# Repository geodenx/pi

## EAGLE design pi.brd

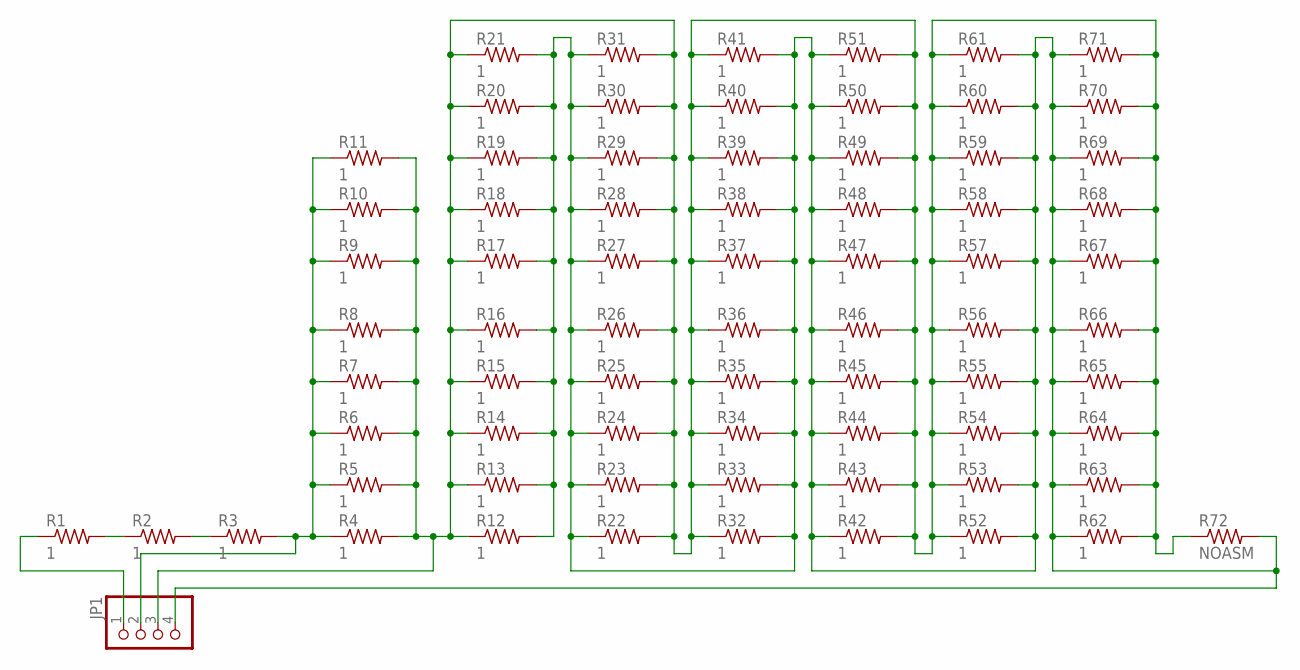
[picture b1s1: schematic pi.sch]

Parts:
JP1: PINHD-1X4; 1X04
R1, R2, R3, R4, R5, R6, R7, R8, R9, R10, R11, R12, R13, R14, R15, R16, R17, R18, R19, R20, R21, R22, R23, R24, R25, R26, R27, R28, R29, R30, R31, R32, R33, R34, R35, R36, R37, R38, R39, R40, R41, R42, R43, R44, R45, R46, R47, R48, R49, R50, R51, R52, R53, R54, R55, R56, R57, R58, R59, R60, R61, R62, R63, R64, R65, R66, R67, R68, R69, R70, R71: 1; R0603
R72: NOASM; R0603

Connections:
unnamed: R1.2, R2.1
unnamed: R2.2, R3.1
unnamed: JP1.4, R12.2, R13.2, R14.2, R15.2, R16.2, R17.2, R18.2, R19.2, R20.2, R21.2, R22.1, R23.1, R24.1, R25.1, R26.1, R27.1, R28.1, R29.1, R30.1, R31.1, R32.2, R33.2, R34.2, R35.2, R36.2, R37.2, R38.2, R39.2, R40.2, R41.2, R42.1, R43.1, R44.1, R45.1, R46.1, R47.1, R48.1, R49.1, R50.1, R51.1, R52.2, R53.2, R54.2, R55.2, R56.2, R57.2, R58.2, R59.2, R60.2, R61.2, R62.1, R63.1, R64.1, R65.1, R66.1, R67.1, R68.1, R69.1, R70.1, R71.1, R72.2
unnamed: JP1.1, R1.1
unnamed: JP1.2, R3.2, R4.1, R5.1, R6.1, R7.1, R8.1, R9.1, R10.1, R11.1
unnamed: JP1.3, R4.2, R5.2, R6.2, R7.2, R8.2, R9.2, R10.2, R11.2, R12.1, R13.1, R14.1, R15.1, R16.1, R17.1, R18.1, R19.1, R20.1, R21.1, R22.2, R23.2, R24.2, R25.2, R26.2, R27.2, R28.2, R29.2, R30.2, R31.2, R32.1, R33.1, R34.1, R35.1, R36.1, R37.1, R38.1, R39.1, R40.1, R41.1, R42.2, R43.2, R44.2, R45.2, R46.2, R47.2, R48.2, R49.2, R50.2, R51.2, R52.1, R53.1, R54.1, R55.1, R56.1, R57.1, R58.1, R59.1, R60.1, R61.1, R62.2, R63.2, R64.2, R65.2, R66.2, R67.2, R68.2, R69.2, R70.2, R71.2, R72.1

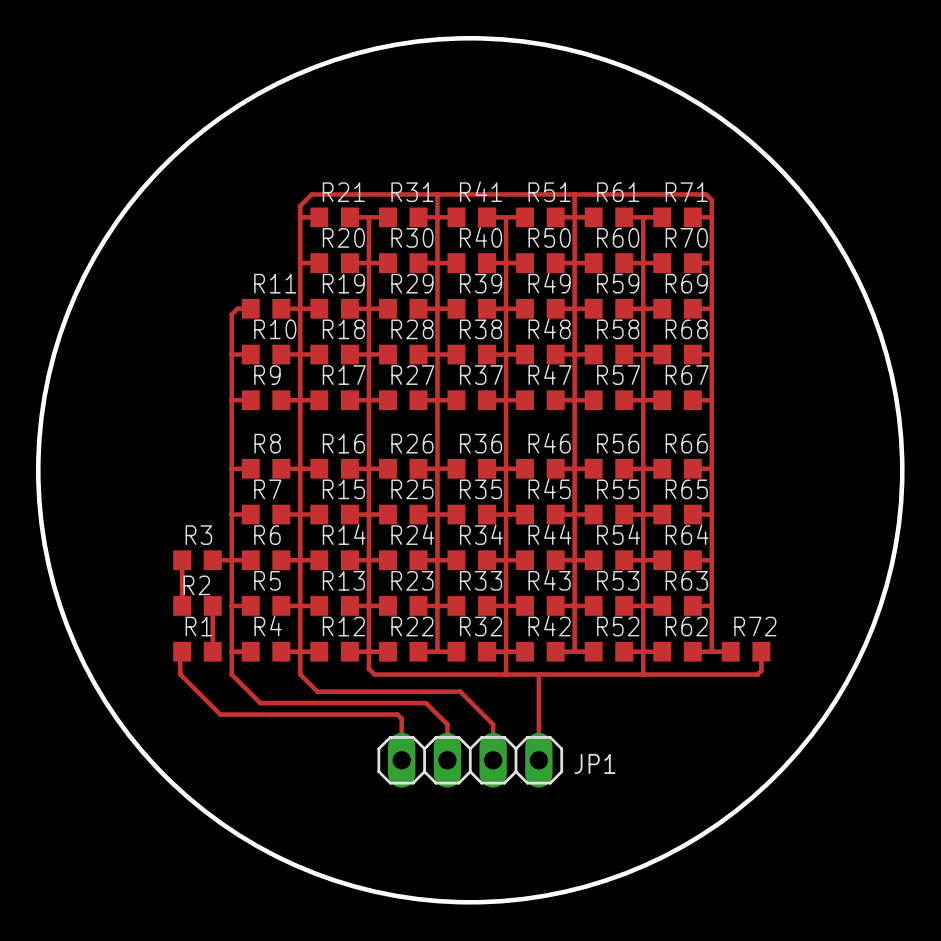
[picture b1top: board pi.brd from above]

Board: 2 copper layers, 48.0 x 48.0 mm, 73 parts (0 on the bottom side), 6 nets.

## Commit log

2015-07-04 Place R network
2015-07-04 Change dimension, eliminate unrouted, add logo
